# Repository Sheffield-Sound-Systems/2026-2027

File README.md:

# Sheffield Sound Systems 2026/27
Home for Sound System's designs of 2026/27
## Adding Designs
### Formatting files
First please format your files so you can upload both your LTspice Schematic and KiCad PCB & schematic in seperate folders appropriately. You should have two folders- one for LTspice design and one for the PCB design:

Within the LTspice folder you should include the **.asc** file of your design and any additonal **external component libraries**:

In the PCB folder you should have the **.kicad_sch, .kicad_pcb & .kicad_pro** files, you can also include the Bill Of Materials (BOM) if you wish: 

### Finding Your Folder
To upload your teams design please find your allocated folder below:
| Team Name |
| ------------- |
| [EXAMPLE](https://github.com/Sheffield-Sound-Systems/2026-2027/tree/main/Designs/Pedal/EXAMPLE)    |
| [Contactless Gesture Expression Pedal](https://github.com/Sheffield-Sound-Systems/2026-2027/tree/main/Designs/Pedal/Contactless%20Gesture%20Expression%20Pedal)    |
| [Delay Effect Pedal](https://github.com/Sheffield-Sound-Systems/2026-2027/tree/main/Designs/Pedal/Delay%20Effect%20Pedal)      |
### Uploading Your Design
Now with your folder located and your schematics and designs in the right format
you can upload your design.
1. Press fork at the top of the page and creat a fork of the repository under your own account:

2. Find your group's folder in your forked repository and press Add file and then Upload files: 

3. Drag and drop the LTspice & KiCad folder into the window.
4. Press Commit changes to save your newly uploaded files to your fork.
5. At the top of the main page on your forked repository press contribute and then open pull request:

6.Add a meaningful title with your group name and what you're adding. Then press create pull request: 

7. Wait for a member of the management team to review the design and approve it.
----------------------------------------------------------
<details>
<summary>Sem-1</summary>
 <table>
        <tr>
          <th>Team Name</th>
        </tr>
        <tr>
          <td><a href= "https://github.com/Sheffield-Sound-Systems/2026-2027/tree/main/Designs/Pedal/Contactless%20Gesture%20Expression%20Pedal">Contactless Gesture Expression Pedal</a></td>
        </tr>
        <tr>
          <td><a href= "https://github.com/Sheffield-Sound-Systems/2026-2027/tree/main/Designs/Pedal/Delay%20Effect%20Pedal">Delay Effect Pedal</a></td>
        </tr>
    </table>
</details>
<details>
<summary>Sem-2</summary>
<table>
        <tr>
          <th>Team Name</th>
        </tr>
        <tr>
          <td><a href= "https://github.com/CyanCertified/Testing-out-github/tree/main/Designs/Pedal/Team%201">Team 1</a></td>
        </tr>
        <tr>
          <td><a href= "https://github.com/CyanCertified/Testing-out-github/tree/main/Designs/Pedal/Team%201">Team 2</a></td>
        </tr>
    </table>
</details>

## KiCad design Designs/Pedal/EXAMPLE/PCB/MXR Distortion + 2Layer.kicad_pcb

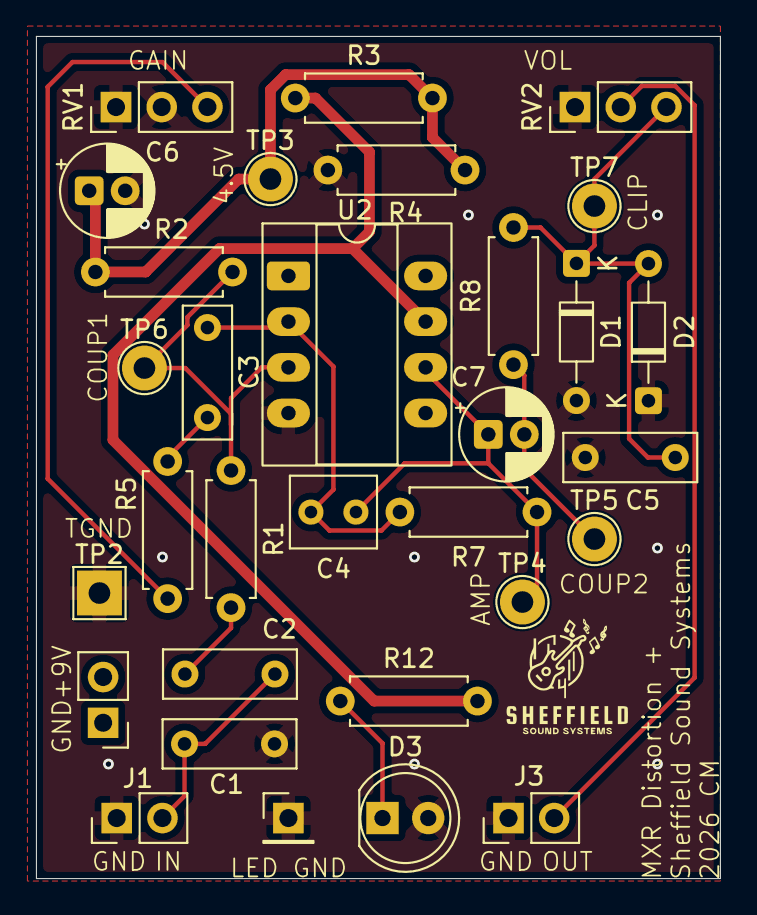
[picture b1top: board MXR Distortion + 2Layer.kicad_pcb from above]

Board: 2 copper layers, 38.0 x 46.8 mm, 31 parts (0 on the bottom side), 14 nets.

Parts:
BT1: Battery_Cell; PinHeader_1x02_P2.54mm_Vertical
C1, C5: 1n; C_Rect_L7.2mm_W2.5mm_P5.00mm
C2: 10n; C_Rect_L7.2mm_W2.5mm_P5.00mm
C3: 47n; C_Rect_L7.2mm_W2.5mm_P5.00mm
C4: 8p; C_Rect_L4.6mm_W3.8mm_P2.50mm_MKS02_FKP02
C6, C7: 1µ; CP_Radial_D5.0mm_P2.00mm
D1, D2: 1N4148; D_DO-34_SOD68_P7.62mm_Horizontal
D3: D; LED_D5.0mm
J1: AudioJack3; PinHeader_1x02_P2.54mm_Vertical
J3: AudioJack2; PinHeader_1x02_P2.54mm_Vertical
R1, R8: 10k; R_Axial_DIN0207_L6.3mm_D2.5mm_P7.62mm_Horizontal
R2, R3, R4, R7: 1Meg; R_Axial_DIN0207_L6.3mm_D2.5mm_P7.62mm_Horizontal
R5: 4.7k; R_Axial_DIN0207_L6.3mm_D2.5mm_P7.62mm_Horizontal
R12: 2.2k; R_Axial_DIN0207_L6.3mm_D2.5mm_P7.62mm_Horizontal
RV1: 1Meg; PinHeader_1x03_P2.54mm_Vertical
RV2: 10k; PinHeader_1x03_P2.54mm_Vertical
TP1: LED_Ground; PinHeader_1x01_P2.54mm_Vertical
TP2: TGround; TestPoint_THTPad_2.5x2.5mm_Drill1.2mm
TP3: T4.5V; TestPoint_THTPad_D2.5mm_Drill1.2mm
TP4: TAmplify; TestPoint_THTPad_D2.5mm_Drill1.2mm
TP5: TCoupler2; TestPoint_THTPad_D2.5mm_Drill1.2mm
TP6: TCoupler1; TestPoint_THTPad_D2.5mm_Drill1.2mm
TP7: TClipping; TestPoint_THTPad_D2.5mm_Drill1.2mm
U2: LM741; CERDIP-8_W7.62mm_SideBrazed_LongPads_Socket

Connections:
0: C1.2, C5.1, C6.2 (B), D1.2 (-), D2.1 (+), D3.2 (-), J1.S, J3.S, R4.2, RV1.1, RV1.2, RV2.1, TP1.1 (1_1), TP2.1 (1_1), U2.4 (V-)
4.5V: C6.1 (A), R2.1, R3.2, R4.1, TP3.1 (1_1)
+9V: R3.1, R12.2, U2.7 (V+)
Amplifier_Out: C7.2 (B), R8.1, TP5.1 (1_1)
Clipper_Circuit: C5.2, D1.1 (+), D2.2 (-), R8.2, RV2.3, TP7.1 (1_1)
Input: R1.1, R2.2, TP6.1 (1_1), U2.3 (+)
unnamed: C2.1, R1.2
unnamed: C3.2, R5.2
unnamed: C4.1, C7.1 (A), R7.2, TP4.1 (1_1), U2.6
unnamed: D3.1 (+), R12.1
unnamed: J3.T, RV2.2
unnamed: R5.1, RV1.3
unnamed: C3.1, C4.2, R7.1, U2.2 (-)
Signal_In: C1.1, C2.2, J1.T
